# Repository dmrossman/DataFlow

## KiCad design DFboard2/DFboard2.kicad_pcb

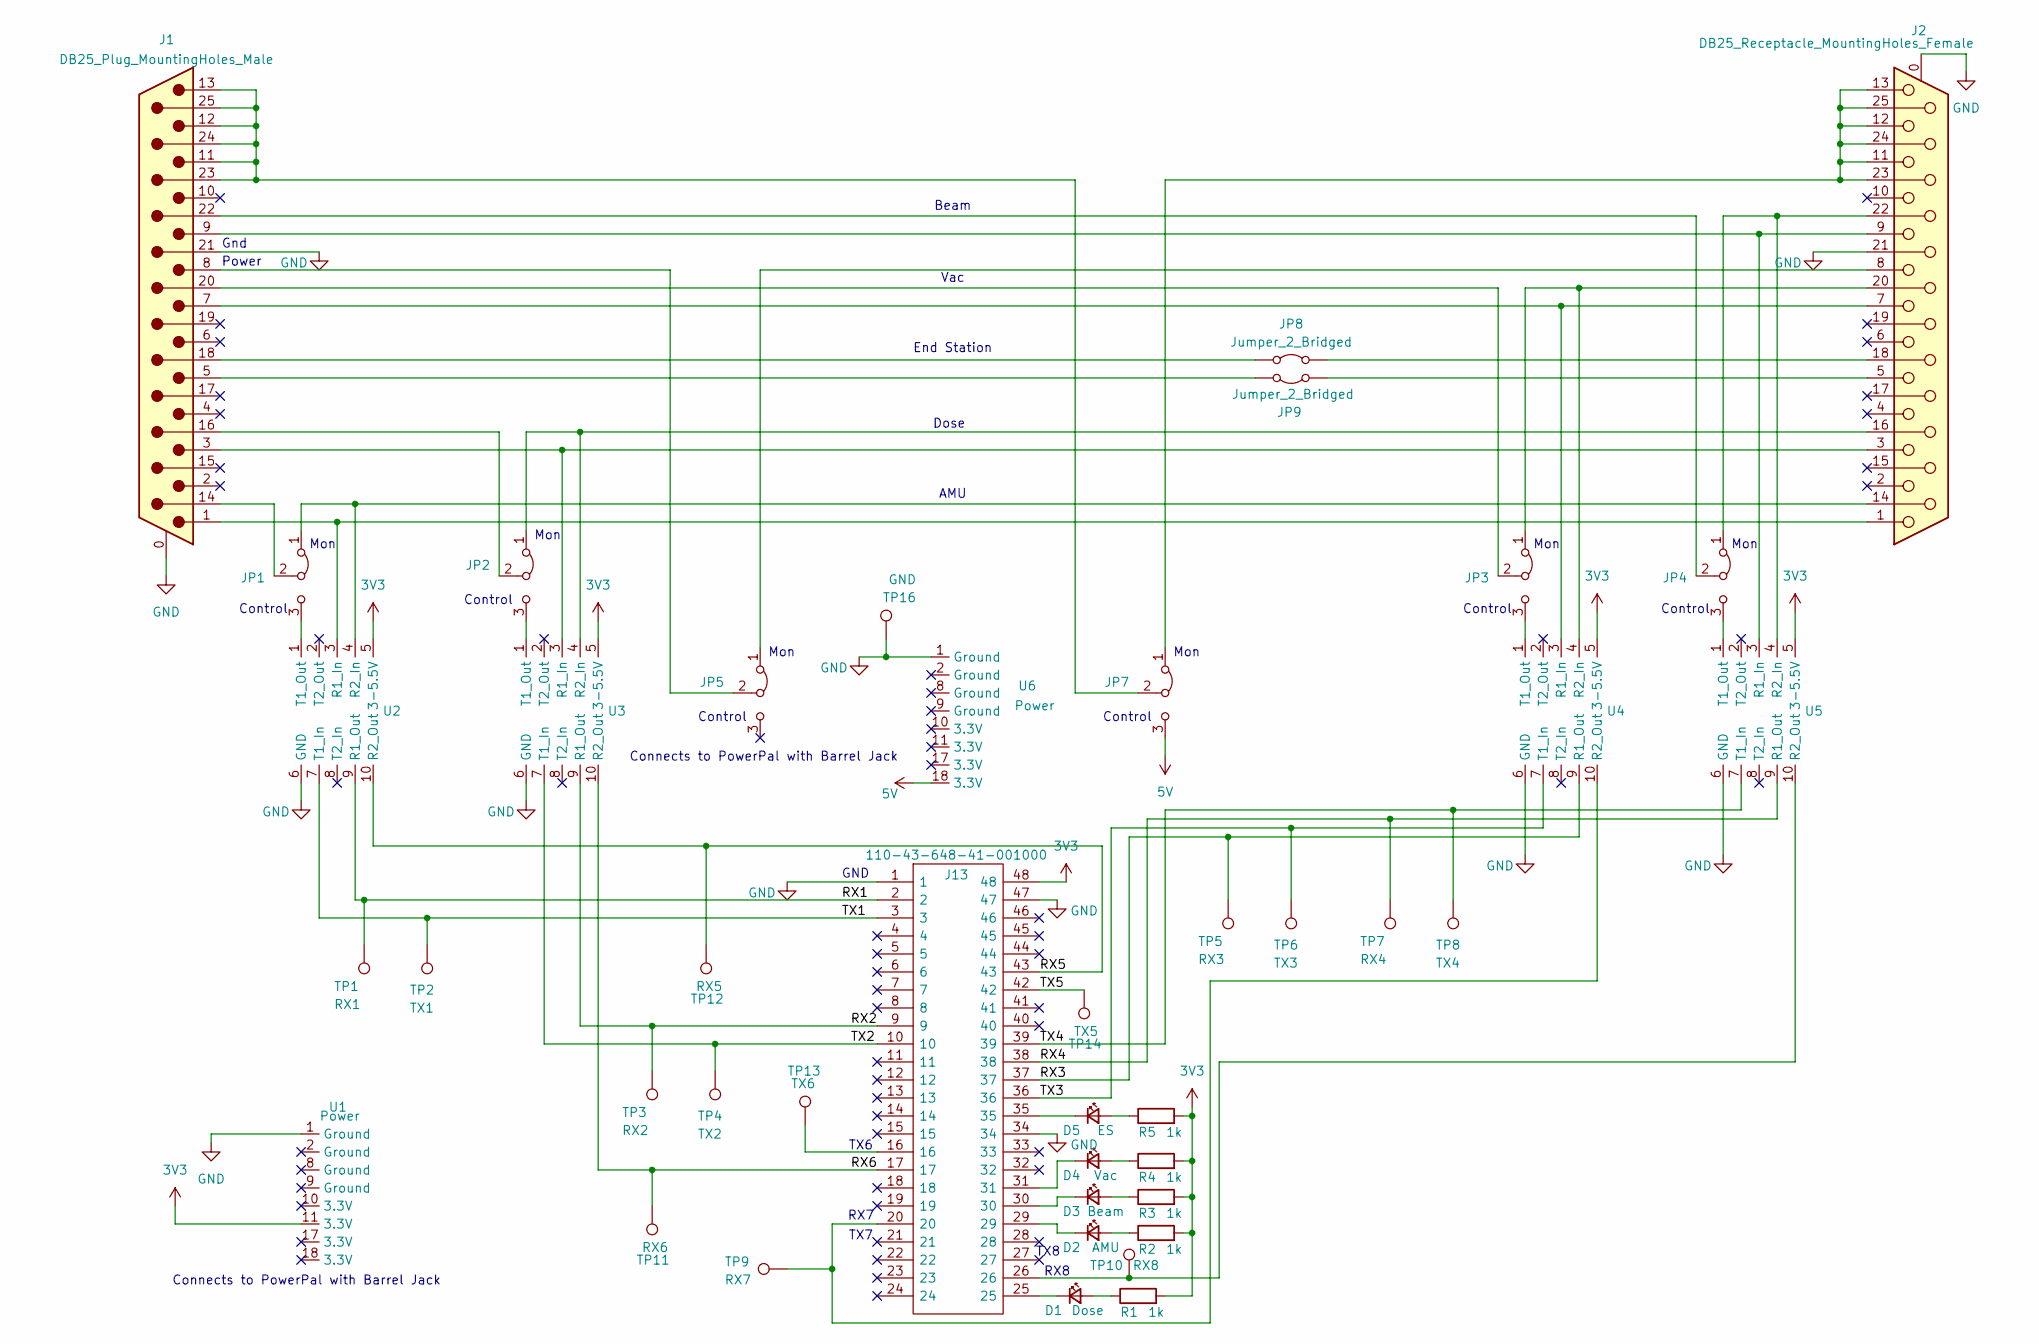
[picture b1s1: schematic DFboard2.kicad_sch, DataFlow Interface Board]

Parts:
D1: Dose; LED_0603
D2: AMU; LED_0603
D3: Beam; LED_0603
D4: Vac; LED_0603
D5: ES; LED_0603
J1: DB25_Plug_MountingHoles_Male; DSUB-25_Male_Horizontal_P2.77x2.84mm_EdgePinOffset4.94mm_Ho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
J2: DB25_Receptacle_MountingHoles_Female; DSUB-25_Female_Horizontal_P2.77x2.84mm_EdgePinOffset4.94mm_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
J13: 110-43-648-41-001000; DIPS1524W51P254L6096H419Q48N; Mouser Part Number 575-11043648
JP1, JP3, JP4: Jumper3; PinHeader_1x03_P2.54mm_Vertical
JP2, JP5, JP7: Jumper_3_Bridged12; PinHeader_1x03_P2.54mm_Vertical
JP8, JP9: Jumper_2_Bridged; PinHeader_1x02_P2.54mm_Vertical
R1, R2, R3, R4, R5: 1k; R_0603_1608Metric
TP1: RX1; PinHeader_1x01_P2.54mm_Vertical
TP2: TX1; PinHeader_1x01_P2.54mm_Vertical
TP3: RX2; PinHeader_1x01_P2.54mm_Vertical
TP4: TX2; PinHeader_1x01_P2.54mm_Vertical
TP5: RX3; PinHeader_1x01_P2.54mm_Vertical
TP6: TX3; PinHeader_1x01_P2.54mm_Vertical
TP7: RX4; PinHeader_1x01_P2.54mm_Vertical
TP8: TX4; PinHeader_1x01_P2.54mm_Vertical
TP9: RX7; PinHeader_1x01_P2.54mm_Vertical
TP10: RX8; PinHeader_1x01_P2.54mm_Vertical
TP11: RX6; PinHeader_1x01_P2.54mm_Vertical
TP12: RX5; PinHeader_1x01_P2.54mm_Vertical
TP13: TX6; PinHeader_1x01_P2.54mm_Vertical
TP14: TX5; PinHeader_1x01_P2.54mm_Vertical
TP16: GND; PinHeader_1x01_P2.54mm_Vertical
U1, U6: Power; PowerPal
U2, U3, U4, U5: Max3232

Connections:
3V3: J13.48, R1.2, R2.2, R3.2, R4.2, R5.2, U1.11 (3.3V), U2.5 (3-5.5V), U3.5 (3-5.5V), U4.5 (3-5.5V), U5.5 (3-5.5V)
5V: JP7.3 (B), U6.18 (3.3V)
/RX1: J13.2, TP1.1, U2.9 (R1_Out)
/RX2: J13.9, TP3.1, U3.9 (R1_Out)
/RX3: J13.37, TP5.1, U4.9 (R1_Out)
/RX4: J13.38, TP7.1, U5.9 (R1_Out)
/RX5: J13.43, TP12.1, U2.10 (R2_Out)
/RX6: J13.17, TP11.1, U3.10 (R2_Out)
/TX1: J13.3, TP2.1, U2.7 (T1_In)
/TX2: J13.10, TP4.1, U3.7 (T1_In)
/TX3: J13.36, TP6.1, U4.7 (T1_In)
/TX4: J13.39, TP8.1, U5.7 (T1_In)
/TX5: J13.42, TP14.1
GND: J1.0 (PAD), J1.21, J2.0 (PAD), J2.21, J13.1, J13.34, J13.47, TP16.1, U1.1 (Ground), U2.6 (GND), U3.6 (GND), U4.6 (GND), U5.6 (GND), U6.1 (Ground)
unnamed: D1.2 (A), R1.1
unnamed: D1.1 (K), J13.25
unnamed: D2.2 (A), R2.1
unnamed: D2.1 (K), J13.29
unnamed: D3.2 (A), R3.1
unnamed: D3.1 (K), J13.30
unnamed: D4.2 (A), R4.1
unnamed: D4.1 (K), J13.31
unnamed: D5.2 (A), R5.1
unnamed: D5.1 (K), J13.35
unnamed: J1.14, JP1.2 (C)
unnamed: J1.16, JP2.2 (C)
unnamed: J1.18, JP8.1 (A)
unnamed: J1.20, JP3.2 (C)
unnamed: J1.22, JP4.2 (C)
unnamed: J1.11, J1.12, J1.13, J1.23, J1.24, J1.25, JP7.2 (C)
unnamed: J2.14, JP1.1 (A), U2.4 (R2_In)
unnamed: J2.16, JP2.1 (A), U3.4 (R2_In)
unnamed: J2.18, JP8.2 (B)
unnamed: J2.20, JP3.1 (A), U4.4 (R2_In)
unnamed: J2.22, JP4.1 (A), U5.4 (R2_In)
unnamed: J2.11, J2.12, J2.13, J2.23, J2.24, J2.25, JP7.1 (A)
unnamed: J13.16, TP13.1
unnamed: JP1.3 (B), U2.1 (T1_Out)
unnamed: JP2.3 (B), U3.1 (T1_Out)
unnamed: JP3.3 (B), U4.1 (T1_Out)
unnamed: JP4.3 (B), U5.1 (T1_Out)
unnamed: J2.8, JP5.1 (A)
unnamed: J1.8, JP5.2 (C)
unnamed: J2.5, JP9.1 (A)
unnamed: J1.5, JP9.2 (B)
unnamed: J1.1, J2.1, U2.3 (R1_In)
unnamed: J1.3, J2.3, U3.3 (R1_In)
unnamed: J1.7, J2.7, U4.3 (R1_In)
unnamed: J13.20, TP9.1, U4.10 (R2_Out)
unnamed: J1.9, J2.9, U5.3 (R1_In)
unnamed: J13.26, TP10.1, U5.10 (R2_Out)

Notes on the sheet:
Connects to PowerPal with Barrel Jack
Power
Control
RX7
Gnd
TX7
Mon
TX8
RX8
Vac
TX6
AMU
GND
Beam
Dose
End Station

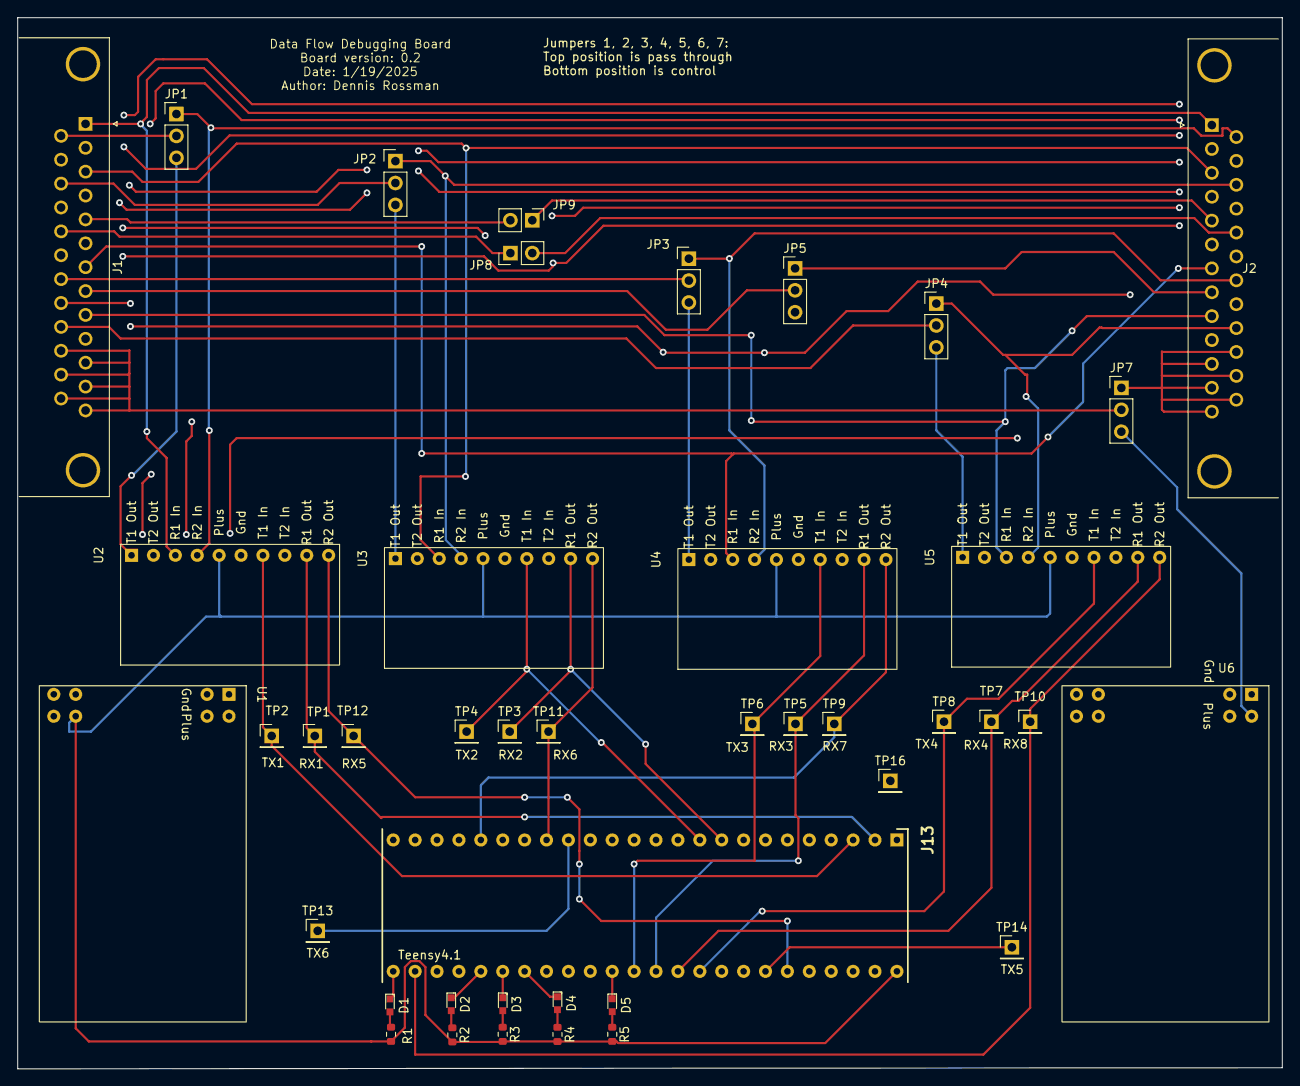
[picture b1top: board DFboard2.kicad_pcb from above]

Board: 2 copper layers, 146.7 x 121.9 mm, 42 parts (0 on the bottom side), 51 nets.

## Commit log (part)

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2024-10-19 Add files via upload
    Added a button to tkinter window to update settings for testing.
2024-10-20 Add files via upload
    Added checksum calculation and value decode. Tksheet isn't updating the displayed values when I call set cell data?
2024-10-20 Add files via upload
    Fixed tksheet update data (if you get the columns and rows in the right order it seems to work, go figure). I created a dictionary for updating all of the fields. Now for testing on the implanter.
2024-10-20 Add files via upload
    Serial handler isn't working. It is not getting in sync... compare to older code to see which change broke something.
2024-10-20 Add files via upload
    Adding arduino files to the repository. Maybe that will give me a clue.
2024-10-20 Add files via upload
    I think I found the issue. The serial port was setup for human readable data and not machine. I think it is fixed. Need to download arduino and try it again.
2024-10-22 Fixed arduino code (machine readable), converted message from bytes to int, fixed typos
    The arduino code was still setup to spit out human readable messages to the serial port. Changed it back to plain binary data.
    Once the message is read in the python script, converted the bytes to int. It is harder to deal with bytes.
    Fixed a typo in the fields dictionary (the from byte needs to be bigger than the start byte... duh).
    Still need to find the e-shower aperature voltage bytes?
    Need to find a way to do formating on the different numbers (ints, floats, scientific notation, strings)
2024-10-23 SerialHandler : changed sync errors, TkSheet : added formats into the value
    SerialHandler - I added logic that if we have the right index but an invalid character, it should throw an error
    TkSheet - I put formats (Decimal, Floating point, Scientific notation, and strings) into the dictionary and changed the decode function to return a string instead of a number
2024-10-25 Fixed some coeffs to fix read backs
    Fixed the coefficients for the pressure settings. Trim looks correct. I don't know why DataFlow shows -1.
2024-10-25 Fixed some missing / incorrect fields in Beam channel
    I went through more data from the SD card and updated some fields that have data. I am not sure what some of it is.
2024-10-25 Delete Decoder Ring 2.xlsx
    All necessary data is in DecoderRing.xlsx
2024-10-29 Starting PCB folder
    Rev 0.1 of the interface board. Plan is to have a board that can both be used for debugging and connecting directly to the implanter.
2024-10-30 Old Teensy board example
2024-11-04 Add files via upload
    Copied old board and made a new MAX3232 board. Need to update the layout.
2024-11-05 Updated MAX3232 Symbol. Started adding jumpers
    I need to verify which channel I should skip (Endstation).
2024-11-09 Finished schematic. Ready for layout.
2024-11-09 Updated Decoder Ring, added Correlations
    Correlations is in here to track how crazy I was getting trying to get a good mapping between the data and the results. This can be deleted later.
2024-11-11 Added test points to schematic. Started pcb layout.
2024-11-18 Submitted board to PCB house
2024-11-30 Board version 0.2 - fixed missing ground
    The ground for the PowerPal was not connected to the ground coming from the implanter and the signals were all over the place.
2024-12-01 Arduino changed to byte count
    Changed the arduino code from looking for a pause between messages to signal the end of the message to just counting bytes. Some of the messages had pauses within the message that were causing issues.
2024-12-01 DataFlow3 doesn't work
    I tried lenghening the delay in DataFlow2 from 20msec to 100msec, but it still has issues. DataFlow3 is getting data, but never sends a message?
2024-12-04 Update DataFlow3.ino
    Fixed pointer references. It has been too long since I have done pointers in C.
2024-12-08 Fixed DataFlow3.ino
    I was setting the message length to zero, but I needed it later. I put the length in a temp variable and changed the add character function to return the message length instead of a boolean.
2024-12-08 Update DataFlow3.ino
    Found one more place where I was using chanIndex instead of msgLength.
2024-12-11 Fixed SDouput format
    Build SD output function was putting the channel in the message length column.
2024-12-12 Update DataFlow3.ino
    Only send the long messages from the implanter to the python script. Also changed the message builder so that if an incorrect byte comes in, the count starts over.
2024-12-14 Merging changes
2024-12-16 Adding time
2024-12-17 Create ParseInt.ino
    Added my own parseint code.
2024-12-17 Update DataFlow3.ino
    Attempting to add RTC functionality.
2024-12-19 Update DataFlow3.ino
    Working on adding RTC
2024-12-31 Add decoder.py - Decode arduino SD card save files
2025-01-02 Multiple updates
    1. Updated decoder ring with information about infrequent messages.
    2. Updated decoder to handle shorter messages.
    3. Updated serial and tksheet to work with time. Discovered that reading time back from the arduino will be... challenging using the current system.
2025-01-02 Updated DataFlow3.ino to add time
    Discovered that sending the RTC back will be challenging.
2025-01-06 SerialTransfer
2025-01-19 Updated PCB - ground plane + leds
2025-01-26 Adding SerialTransfer and TimeSet files
2025-01-26 Back at it...
2025-01-27 Finally getting serialtransfer to work
2025-01-31 Working on PySerialTransfer
2025-02-02 Redid DataFlow4 w/out SerialHandler
2025-02-02 Added extra LEDs and Heartbeat
2025-02-03 Fixing channel id's
2025-02-09 Hopefully fixed tksheet crashes
2025-02-15 Troubleshooting lack of messages to python
2025-02-17 SD card is affecting serial transfers. Fix?
2025-02-19 Got SDcard delay to work. Other fixes didn't fix checksum errors.
2025-02-19 Fixed checksum issue.
2025-02-20 Trying to fix SD card format, remove extra lines
2025-02-23 Added a logging file
2025-02-23 Fixed error in checksum in tksheet. Attempting to fix no serial connection.
2025-02-24 Sync local to repo
2025-02-25 Sync with repo
2025-02-27 Decoder ring updates for Dose.
2025-02-27 Added recipe, idl, manual directories
2025-02-28 Redid Serial for USB
2025-03-02 Working on DataFlow messages
2025-03-02 Continuing to decode DataFlow command messages.
2025-03-03 Updated recipe write function. Cleaned up files.
2025-03-05 Created idl.py - needs work
2025-03-06 Update decode.
2025-03-14 Created idl.py with GitHub- needs work
2025-03-15 Create decoder2.py
    This is to pull the data so that each seconds data samples will be in the same row.
2025-03-19 Working on decoder2 to put data into columns
2025-03-23 No changes
2025-03-25 Decoder2 looks like it is working.
2025-03-29 idl read and write work
    Except for snapdata.txt. I can add that later if there is a need.
2025-03-30 Cleaned up old files
    Cleaned up old files
2025-04-02 Created decoder3 to pull implant data out
2025-04-11 Created b decoder vs.s with makeFloat
2025-04-13 Update decoder
2025-04-13 tksheet decoder work
2025-04-14 Update decoder - fix vaporizer error
    I didn't fix the root cause, just the symptom
2025-04-14 Updated decoder3b - added scaler
2025-08-17 Adding IDL data files
2025-08-18 Minor edits
2025-08-19 Minor tweaks
2025-08-21 Started work on IDL comparison
2025-08-21 Not done yet
2025-08-30 Working on decoder
2025-08-30 Added data for March. Too big?
2025-09-03 Done with decoder (for now)
2026-06-13 Decoder5
    Created decoder5 to decode the data to idl type files for comparison
